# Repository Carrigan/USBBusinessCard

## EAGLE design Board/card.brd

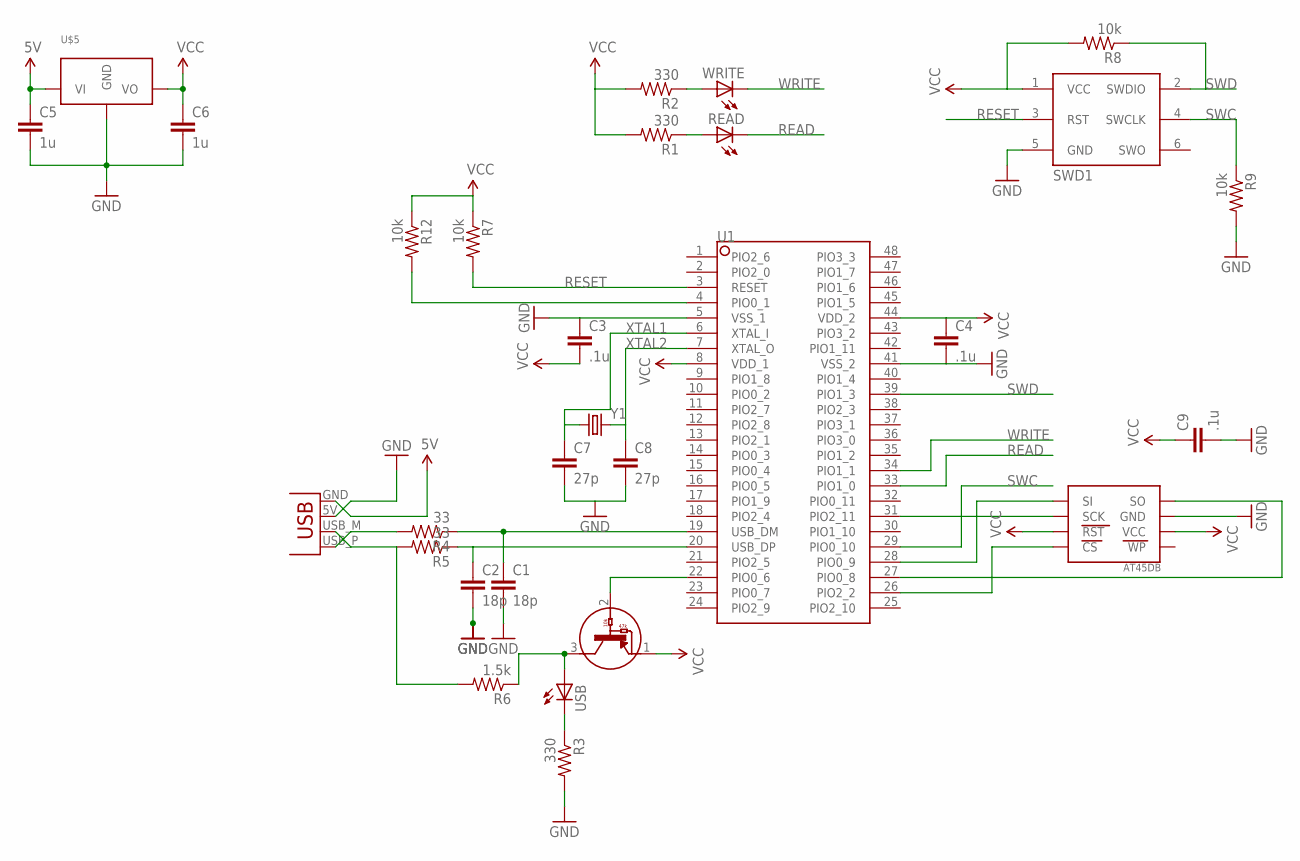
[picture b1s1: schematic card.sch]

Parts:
AT45DB: AT45DBXXXD; SOIC8
C1, C2: 18p; 0805
C3, C4: .1u; 1206
C5, C6: 1u; 0805
C7, C8: 27p; 0805
C9: .1u; 0805
JP1: USBPCB; USB-A-PCB
R1, R2, R3: 330; 0805
R4, R5: 33; 0805
R6: 1.5k; 0805
R7, R8, R9, R12: 10k; 0805
READ: LED1206; LED-1206
SWD1: TC2030CTX_NL; TC2030-NL
U1: LPC1343FBD48; LQFP48
U3: DTA114YKA
U$5: 3_3V_REG; SOT23
USB: LED1206; LED-1206
WRITE: LED1206; LED-1206
Y1: CRYSTAL5X3; CRYSTAL-SMD-5X3

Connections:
5V: C5.1, JP1.GND, U$5.1 (VI)
GND: AT45DB.7 (GND), C1.2, C2.2, C3.1, C4.2, C5.2, C6.2, C7.2, C8.2, C9.2, JP1.5V (VBUS), R3.2, R9.2, SWD1.5 (GND), U1.5 (VSS_1), U1.41 (VSS_2), U$5.3 (GND)
unnamed: C1.1, R4.1, U1.19 (USB_DM)
unnamed: JP1.USB_M (D-), R5.2, R6.2
unnamed: C2.1, R5.1, U1.20 (USB_DP)
unnamed: AT45DB.2 (SCK), U1.31 (PIO2_11)
unnamed: R1.1, READ.A
unnamed: AT45DB.8 (SO), U1.27 (PIO0_8)
unnamed: R2.1, WRITE.A
unnamed: R6.1, U3.3, USB.A
unnamed: R3.1, USB.C
unnamed: U1.22 (PIO0_6), U3.2
unnamed: AT45DB.4 (CS), U1.26 (PIO2_2)
unnamed: R12.2, U1.4 (PIO0_1)
unnamed: JP1.USB_P (D+), R4.2
READ: READ.C, U1.33 (PIO1_0)
RESET: R7.2, SWD1.3 (RST), U1.3 (RESET)
SWC: R9.1, SWD1.4 (SWCLK), U1.29 (PIO0_10)
SWD: R8.1, SWD1.2 (SWDIO), U1.39 (PIO1_3)
SWV: AT45DB.1 (SI), U1.28 (PIO0_9)
VCC: AT45DB.3 (RST), AT45DB.6 (VCC), C3.2, C4.1, C6.1, C9.1, R1.2, R2.2, R7.1, R8.2, R12.1, SWD1.1 (VCC), U1.8 (VDD_1), U1.44 (VDD_2), U3.1, U$5.2 (VO)
WRITE: U1.34 (PIO1_1), WRITE.C
XTAL1: C7.1, U1.6 (XTAL_I), Y1.1
XTAL2: C8.1, U1.7 (XTAL_O), Y1.3 (2)

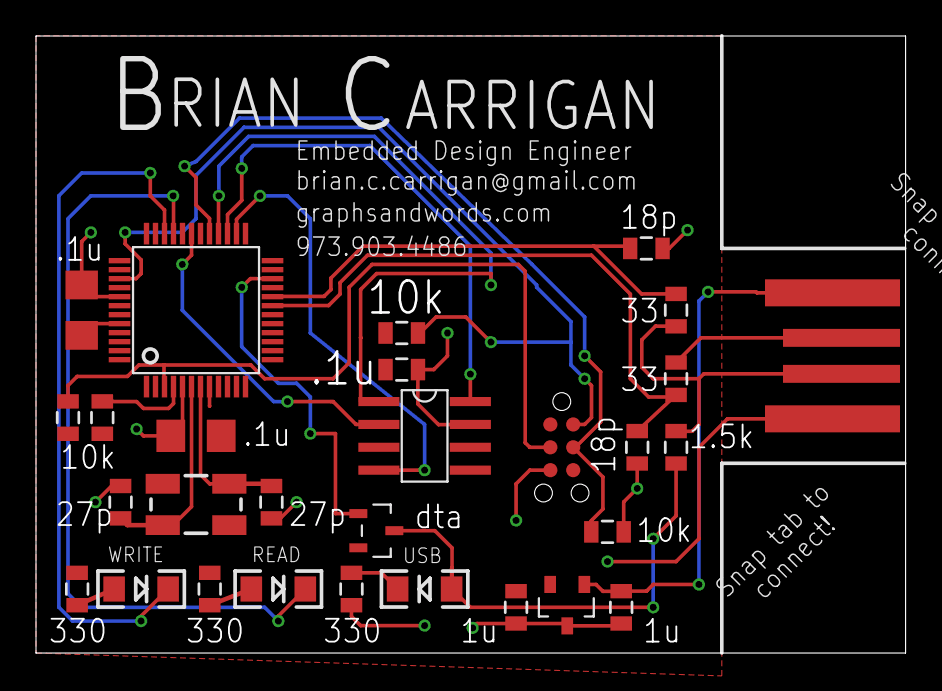
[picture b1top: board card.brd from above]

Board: 2 copper layers, 48.3 x 34.4 mm, 29 parts (0 on the bottom side), 24 nets.

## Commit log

2013-02-01 Created a repository for this project from the code posted on graphsandwords.com
2013-03-06 Fixed a few math errors and improved write speeds.
2013-08-16 Added Eagle files.
2017-05-29 Add in the BOM here.

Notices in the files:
parts and their libraries:
SparkFun-Connectors: Licensing: CC v3.0 Share-Alike You are welcome to use this library for commercial purposes.
